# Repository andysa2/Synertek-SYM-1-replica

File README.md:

# Synertek SYM-1 PCB replica

Board outline, footprints and silkscreen for a Synertek SYM-1 replica, in Kicad format.

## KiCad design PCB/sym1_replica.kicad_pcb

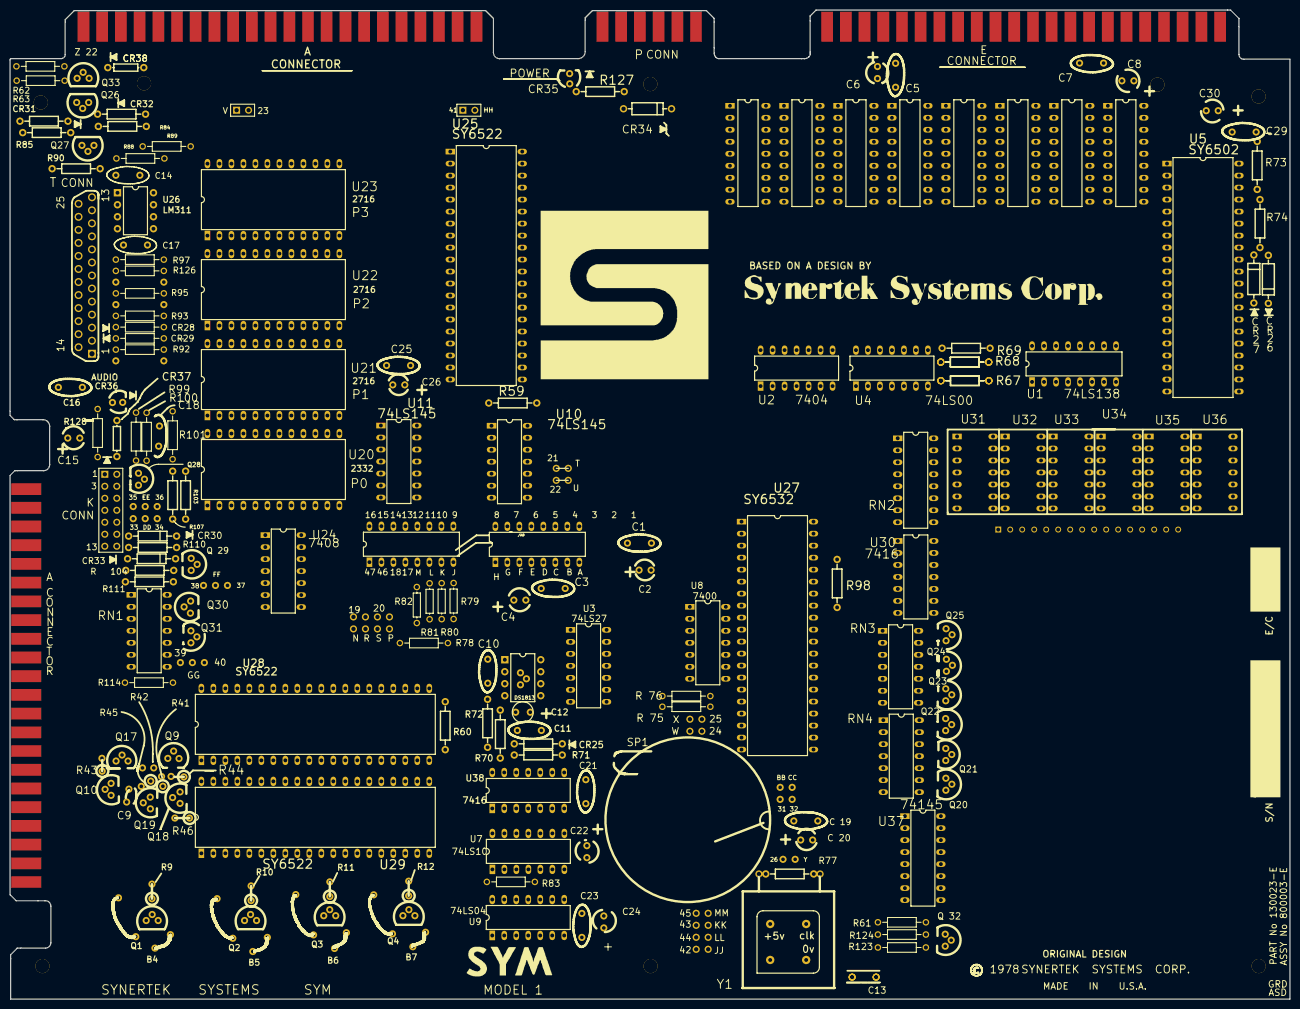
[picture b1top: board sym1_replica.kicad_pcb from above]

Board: 2 copper layers, 271.0 x 209.4 mm, 42 parts (0 on the bottom side), 18 nets, no tracks yet.

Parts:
2332, 2716, 2716#2, 2716#3: Comment; dip24
CR25, CR31, CR32: AXIAL0.4
CR28, CR29: Comment; AXIAL-0.4
R59, R60, R70, R71, R72, R84, R85, R90, R98, R103, R107, R127: AXIAL0.4
R62, R63, R88, R89, R92, R93, R95, R97, R126, R128: Comment; AXIAL-0.4
R67, R68, R69: Comment; AXIAL0.4
U5: SY6502; dip40
U10, U11: 74LS145; DIP14
U25, U28, U29: SY6522; dip40
U26: LM311; DIP8
U38: 7416; DIP14

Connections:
0V: R62.1, U5.1, U5.21, U25.1, U25.40, U28.1, U29.1, U38.7
5V: U5.8, U25.20, U28.20, U29.20
A0: U5.9, U25.38
A1: U5.10, U25.37
A2: U5.11, U25.36
A3: U5.12, U25.35
D0: U5.33, U25.33
D1: U5.32, U25.32
D2: U5.31, U25.31
D3: U5.30, U25.30
D4: U5.29, U25.29
D5: U5.28, U25.28
D6: U5.27, U25.27
D7: U5.26, U25.26
IRQ: U5.4, U25.21, U28.21, U29.21
P2: U25.25, U28.25, U29.25
RST: U5.40, U25.34, U28.34, U29.34
RW: U25.22, U28.22, U29.22
